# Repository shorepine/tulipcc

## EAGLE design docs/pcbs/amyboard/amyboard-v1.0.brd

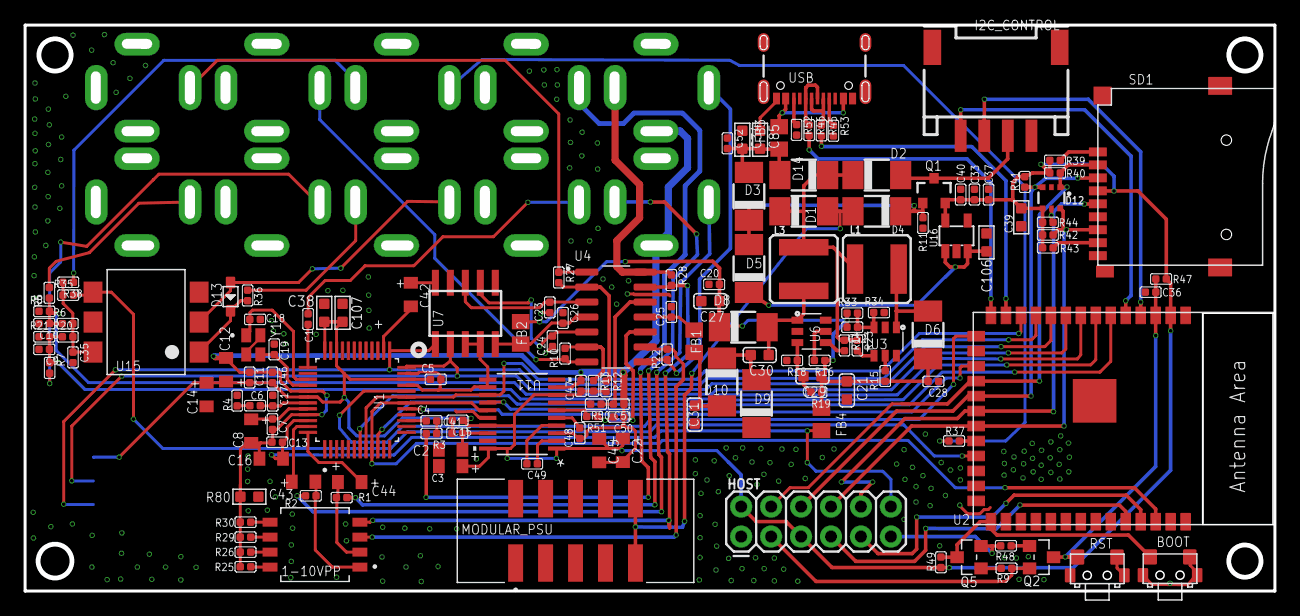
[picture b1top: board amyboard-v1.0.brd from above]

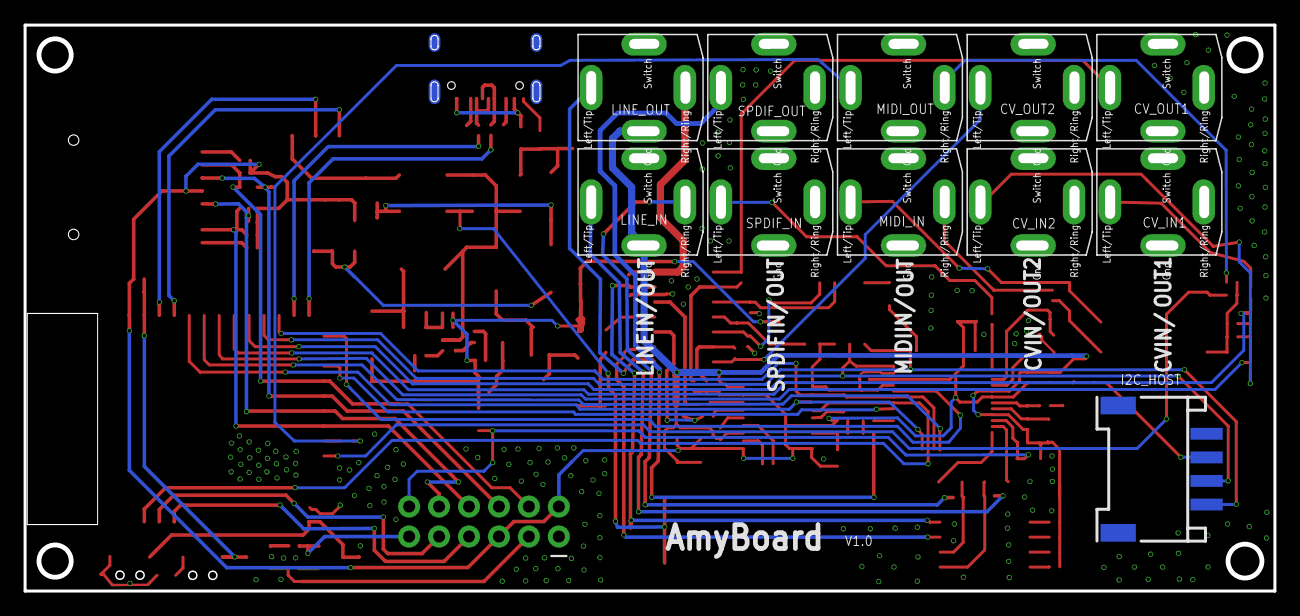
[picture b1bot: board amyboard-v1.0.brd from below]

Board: 2 copper layers, 106.0 x 48.0 mm, 155 parts (11 on the bottom side), 105 nets.

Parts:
1-10VPP: 218-4LPSTR; SW_218-4LPSTR
BOOT: TS24CA; 2*4*3.5MM
C1, C4, C5, C7, C11, C13, C15, C20, C23, C24, C25, C26, C28, C33, C35, C36, C37, C40, C41, C46, C47, C52: 100nF; DISCRETE_C0402
C2, C3, C8, C12, C14, C16, C22, C42, C43, C44, C45: 10uF/10V/TAN; SMC_Z
C6: 68nF; DISCRETE_C0402
C9, C10: 1nF; DISCRETE_C0402
C17: 4.7nF; DISCRETE_C0402
C18, C19: 10pF; DISCRETE_C0402
C21, C27, C30, C31: 22uF; C0603
C29: 22pF; C0603
C32: 22pF; DISCRETE_C0402
C34, C38, C39, C85: 10uF; DISCRETE_C0603
C48, C49: 2.2uF; DISCRETE_C0402
C50, C51: 2.2nF; DISCRETE_C0402
C106: 4.7uF/16V; 0603
C107: 10uF; 0603
CV_IN1, CV_IN2: NV-PJ3410_STEREO; NV-PJ3410_SOCKET
CV_OUT1, CV_OUT2: NV-PJ3410_STEREO; NV-PJ3410_SOCKET
D1, D2, D3, D4, D5, D6, D8, D9, D10, D14: SS54; DO-214AC
D12: SMF05C; SOT363
D13: 1N4148WS; SOD323
FB1, FB2, FB3, FB4: 100Mhz@120R; R0805
HOST: 2X6 FEMALE; 2X6
I2C_CONTROL, I2C_HOST: HW4-SMD-2.0-90D
L1: 4.7µH/±30%/3.4A; CR54
L3: 3.3µH/±30%/3.4A; CR54
LINE_IN: NV-PJ3410_STEREO; NV-PJ3410_SOCKET
LINE_OUT: NV-PJ3410_STEREO; NV-PJ3410_SOCKET
MIDI_IN: NV-PJ3410_STEREO; NV-PJ3410_SOCKET
MIDI_OUT: NV-PJ3410_STEREO; NV-PJ3410_SOCKET
MODULAR_PSU: 52601-G10-8LF; AMPHENOL_52601-G10-8LF
PCM5101: U11; PW20_TEX
Q1: AO3407; SOT23-3
Q2, Q5: S8050; SOT23
R1, R2, R22, R28: 51K; DISCRETE_R0402
R3: 150R; DISCRETE_R0402
R4: 680R; DISCRETE_R0402
R5, R7, R10, R27: 30K; DISCRETE_R0402
R6, R9, R12, R13, R20, R39, R40, R41, R42, R43, R47, R48, R49: 10K; DISCRETE_R0402
R8, R21, R34: 15K; DISCRETE_R0402
R11, R14, R23: 100K; DISCRETE_R0402
R15, R16: 0R; DISCRETE_R0402
R18: 12K; DISCRETE_R0402
R19: 228K; DISCRETE_R0402
R25, R26, R29, R30: 22K; DISCRETE_R0402
R33: 110K; DISCRETE_R0402
R35, R50, R51: 470R; DISCRETE_R0402
R36: 220R; DISCRETE_R0402
R37: 10R; DISCRETE_R0402
R38: 33R; DISCRETE_R0402
R44: NC; DISCRETE_R0402
R45, R46: 51R; DISCRETE_R0402
R52, R53: 5.1K; DISCRETE_R0402
R80: 0R; DISCRETE_R0603
RST: TS24CA; 2*4*3.5MM
SD1: SD; 9P-SMD-W/-RING
SPDIF_IN: NV-PJ3410_STEREO; NV-PJ3410_SOCKET
SPDIF_OUT: NV-PJ3410_STEREO; NV-PJ3410_SOCKET
U1: PCM9211PT; QFP50P900X900X160-48N
U2: ESP32­S2­SOLO; ESP32-­S2-­SOLO
U3, U6: HX3608; SOT-23-6
U4: TL074CD; SOIC127P600X175-14N
U7: GP8413; SOIC-10
U15: H11L1SR2M; SOP-6-2.54MM
U16: SPX3819; SOT23-5
USB: USB-C; USB-C-16P-5
Y1: 22.5792MHZ; XTAL_ABM10W-22.5792MHZ-8-K1Z-T3

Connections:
3.3V: C35.1, R6.2, R20.2, R35.1, R38.2, U15.6
3V3_IN: D2.A, I2C_CONTROL.3, Q1.3
5V: C13.1, C16.+, FB4.2, HOST.12, U1.46
5V_IN: C34.2, C52.2, C85.2, D3.A, D14.A, FB3.2
12V: C20.2, C21.1, C27.1, C28.2, C29.1, C32.2, D6.C, D8.C, FB2.1, FB4.1, R15.1, R16.1, R19.1, R33.1
12_IN: D1.A, D4.A, MODULAR_PSU.09, MODULAR_PSU.10
+3V3: C3.+, C5.1, C11.1, C12.+, C14.+, C15.1, C22.+, C33.2, C37.2, C38.1, C39.2, C40.1, C45.+, C46.1, C47.1, C107.1, D12.4, HOST.2, HOST.5, I2C_HOST.3, PCM5101.1, PCM5101.8, PCM5101.17, PCM5101.20, Q1.2, R12.2, R13.2, R39.2, R40.2, R41.2, R42.2, R43.2, R44.2, R47.2, R49.2, SD1.4, U1.22, U1.34, U1.36, U1.42, U2.2, U16.5
+12V: C26.2, FB2.2, U4.4, U7.5
-12V: C25.1, FB1.2, U4.11
ADC1: C10.1, R5.1, R6.1, R8.2, U2.9
ADC2: C9.1, R7.1, R20.1, R21.2, U2.8
AGND: C7.2, C8.-, C11.2, C12.-, C13.2, C16.-, C22.-, C45.-, C46.2, C47.2, C48.1, C50.1, C51.1, LINE_IN.GND, LINE_OUT.GND, PCM5101.3, PCM5101.9, R25.1, R26.1, R29.1, R30.1, R80.1, U1.41, U1.45
AMYIN: U1.17, U2.17
AMYOUT: PCM5101.14, U1.10, U2.6
AMY_FOLLOWER_SCL: I2C_CONTROL.1, U2.5
AMY_FOLLOWER_SDA: I2C_CONTROL.2, U2.4
BCLK: PCM5101.13, U1.8, U1.19, U2.12
CV_OUT1: CV_OUT1.LEFT/TIP, R27.1, U4.1
CV_OUT2: CV_OUT2.LEFT/TIP, R10.1, U4.7
DTR: HOST.11, Q5.2, R48.2
ENABLE: R14.2, U6.4
ENABLE1: R23.2, U3.4
GND: BOOT.1, BOOT.3, BOOT.4, C2.-, C3.-, C5.2, C9.2, C10.2, C14.-, C15.2, C17.1, C18.1, C19.1, C20.1, C21.2, C23.1, C24.1, C25.2, C26.1, C27.2, C28.1, C31.1, C33.1, C34.1, C35.2, C36.1, C37.1, C38.2, C39.1, C40.2, C41.1, C42.-, C52.1, C85.1, C106.2, C107.2, CV_IN1.GND, CV_IN2.GND, CV_OUT1.GND, CV_OUT2.GND, D9.C, D12.2, HOST.1, I2C_CONTROL.4, I2C_CONTROL.SS1, I2C_CONTROL.SS2, I2C_HOST.4, I2C_HOST.SS1, I2C_HOST.SS2, MIDI_IN.GND, MIDI_OUT.GND, MODULAR_PSU.01, MODULAR_PSU.02, MODULAR_PSU.03, MODULAR_PSU.04, MODULAR_PSU.05, MODULAR_PSU.06, MODULAR_PSU.07, MODULAR_PSU.08, PCM5101.10, PCM5101.11, PCM5101.12, PCM5101.16, PCM5101.19, R4.2, R8.1, R11.1, R18.2, R21.1, R34.2, R52.2, R53.2, R80.2, RST.1, RST.3, RST.4, SD1.6, SD1.G1, SD1.G2, SD1.G3, SD1.G4, SPDIF_IN.GND, SPDIF_OUT.GND, U1.21, U1.23, U1.26, U1.27, U1.38, U2.1, U2.40, U2.41, U3.2, U6.2, U7.3, U7.4, U7.6, U7.9, U15.5, U16.2, USB.GND, USB.GND2, Y1.2, Y1.4
I2C_SCL: I2C_HOST.1, U1.25, U2.11, U7.1
I2C_SDA: I2C_HOST.2, U1.24, U2.10, U7.2
IO0: BOOT.2, Q5.3, R49.1, U2.27
IO19: R45.2, U2.13
IO20: R46.2, U2.14
LIN: LINE_IN.LEFT/TIP, R2.2
LINX: C43.+, U1.47
LOUT: LINE_OUT.LEFT/TIP, R22.1, U4.8
LOUT_2V: C50.2, R51.1, U4.10
LRC: PCM5101.15, U1.9, U1.18, U2.38
MCLK: U1.20, U2.15
MIDI_IN: R35.2, U2.23, U15.4
MIDI_OUT: R37.2, U2.22
MPIO: U1.7, U2.7
unnamed: C1.1, U1.37
unnamed: C4.2, R3.1
unnamed: C4.1, U1.15
unnamed: 1-10VPP.1, C43.-, R2.1
unnamed: 1-10VPP.2, C44.-, R1.1
unnamed: C7.1, C8.+, U1.44
unnamed: C6.2, C17.2, U1.43
unnamed: C6.1, R4.1
unnamed: CV_IN2.LEFT/TIP, R7.2
unnamed: D6.A, L1.P$2, U3.1
unnamed: C31.2, D10.A, FB1.1
unnamed: C23.2, U4.3, U7.8
unnamed: CV_IN1.LEFT/TIP, R5.2
unnamed: C24.2, U4.5, U7.7
unnamed: C30.1, D8.A, L3.P$2, U6.1
unnamed: C42.+, U7.10
unnamed: D3.C, D4.C, D5.A, Q1.1, R11.2
unnamed: C106.1, D5.C, U16.1, U16.3
unnamed: C32.1, R33.2, R34.1, U3.3
unnamed: C29.2, R18.1, R19.2, U6.3
unnamed: R16.2, U6.5
unnamed: C30.2, D9.A, D10.C
unnamed: R10.2, R13.1, U4.6
unnamed: R15.2, U3.5
unnamed: R12.1, R27.2, U4.2
unnamed: Q2.1, R48.1
unnamed: 1-10VPP.5, R30.2
unnamed: 1-10VPP.6, R29.2
unnamed: Q5.1, R9.1
unnamed: R53.1, USB.A5
unnamed: R52.1, USB.B5
unnamed: 1-10VPP.8, R25.2
unnamed: 1-10VPP.7, R26.2
unnamed: FB3.1, USB.VBUS1, USB.VBUS2
unnamed: 1-10VPP.3, R22.2, U4.9
unnamed: 1-10VPP.4, R28.2, U4.13
unnamed: C2.+, C41.2, PCM5101.18
unnamed: PCM5101.7, R50.2
unnamed: C49.2, PCM5101.4
unnamed: C49.1, PCM5101.2
unnamed: D13.+, MIDI_IN.LEFT/TIP, U15.2
unnamed: MIDI_IN.RIGHT/RING, R36.1
unnamed: D13.-, R36.2, U15.1
unnamed: MIDI_OUT.LEFT/TIP, R37.1
unnamed: MIDI_OUT.RIGHT/RING, R38.1
unnamed: R39.1, SD1.1
unnamed: R43.1, SD1.8
OUTL: PCM5101.6, R51.2
RESET: C36.2, Q2.3, R47.1, RST.2, U2.3
RIN: LINE_IN.RIGHT/RING, R1.2
RINX: C44.+, U1.48
ROUT: LINE_OUT.RIGHT/RING, R28.1, U4.14
ROUT_2V: C51.2, R50.1, U4.12
RTS: HOST.3, Q2.2, R9.2
RXD/IO44: HOST.7, U2.36
SPDIFIN_SIGNAL: C1.2, SPDIF_IN.LEFT/TIP
SPDIFOUT_SIGNAL: R3.2, SPDIF_OUT.LEFT/TIP
SPI0_CS0: D12.1, HOST.4, R40.1, SD1.2, U2.18
SPI0_MISO: D12.6, HOST.8, R42.1, SD1.7, U2.21
SPI0_MOSI: D12.3, HOST.6, R41.1, SD1.3, U2.19
SPI0_SCK: D12.5, HOST.10, R44.1, SD1.5, U2.20
TXD/IO43: HOST.9, U2.37
USB_D+: R46.1, USB.A6, USB.B6
USB_D-: R45.1, USB.A7, USB.B7
VNEG: C48.2, PCM5101.5
VPWR: D1.C, D2.C, D14.C, L1.P$1, L3.P$1, R14.1, R23.1
XTI: C18.2, U1.39, Y1.1
XTO: C19.2, U1.40, Y1.3

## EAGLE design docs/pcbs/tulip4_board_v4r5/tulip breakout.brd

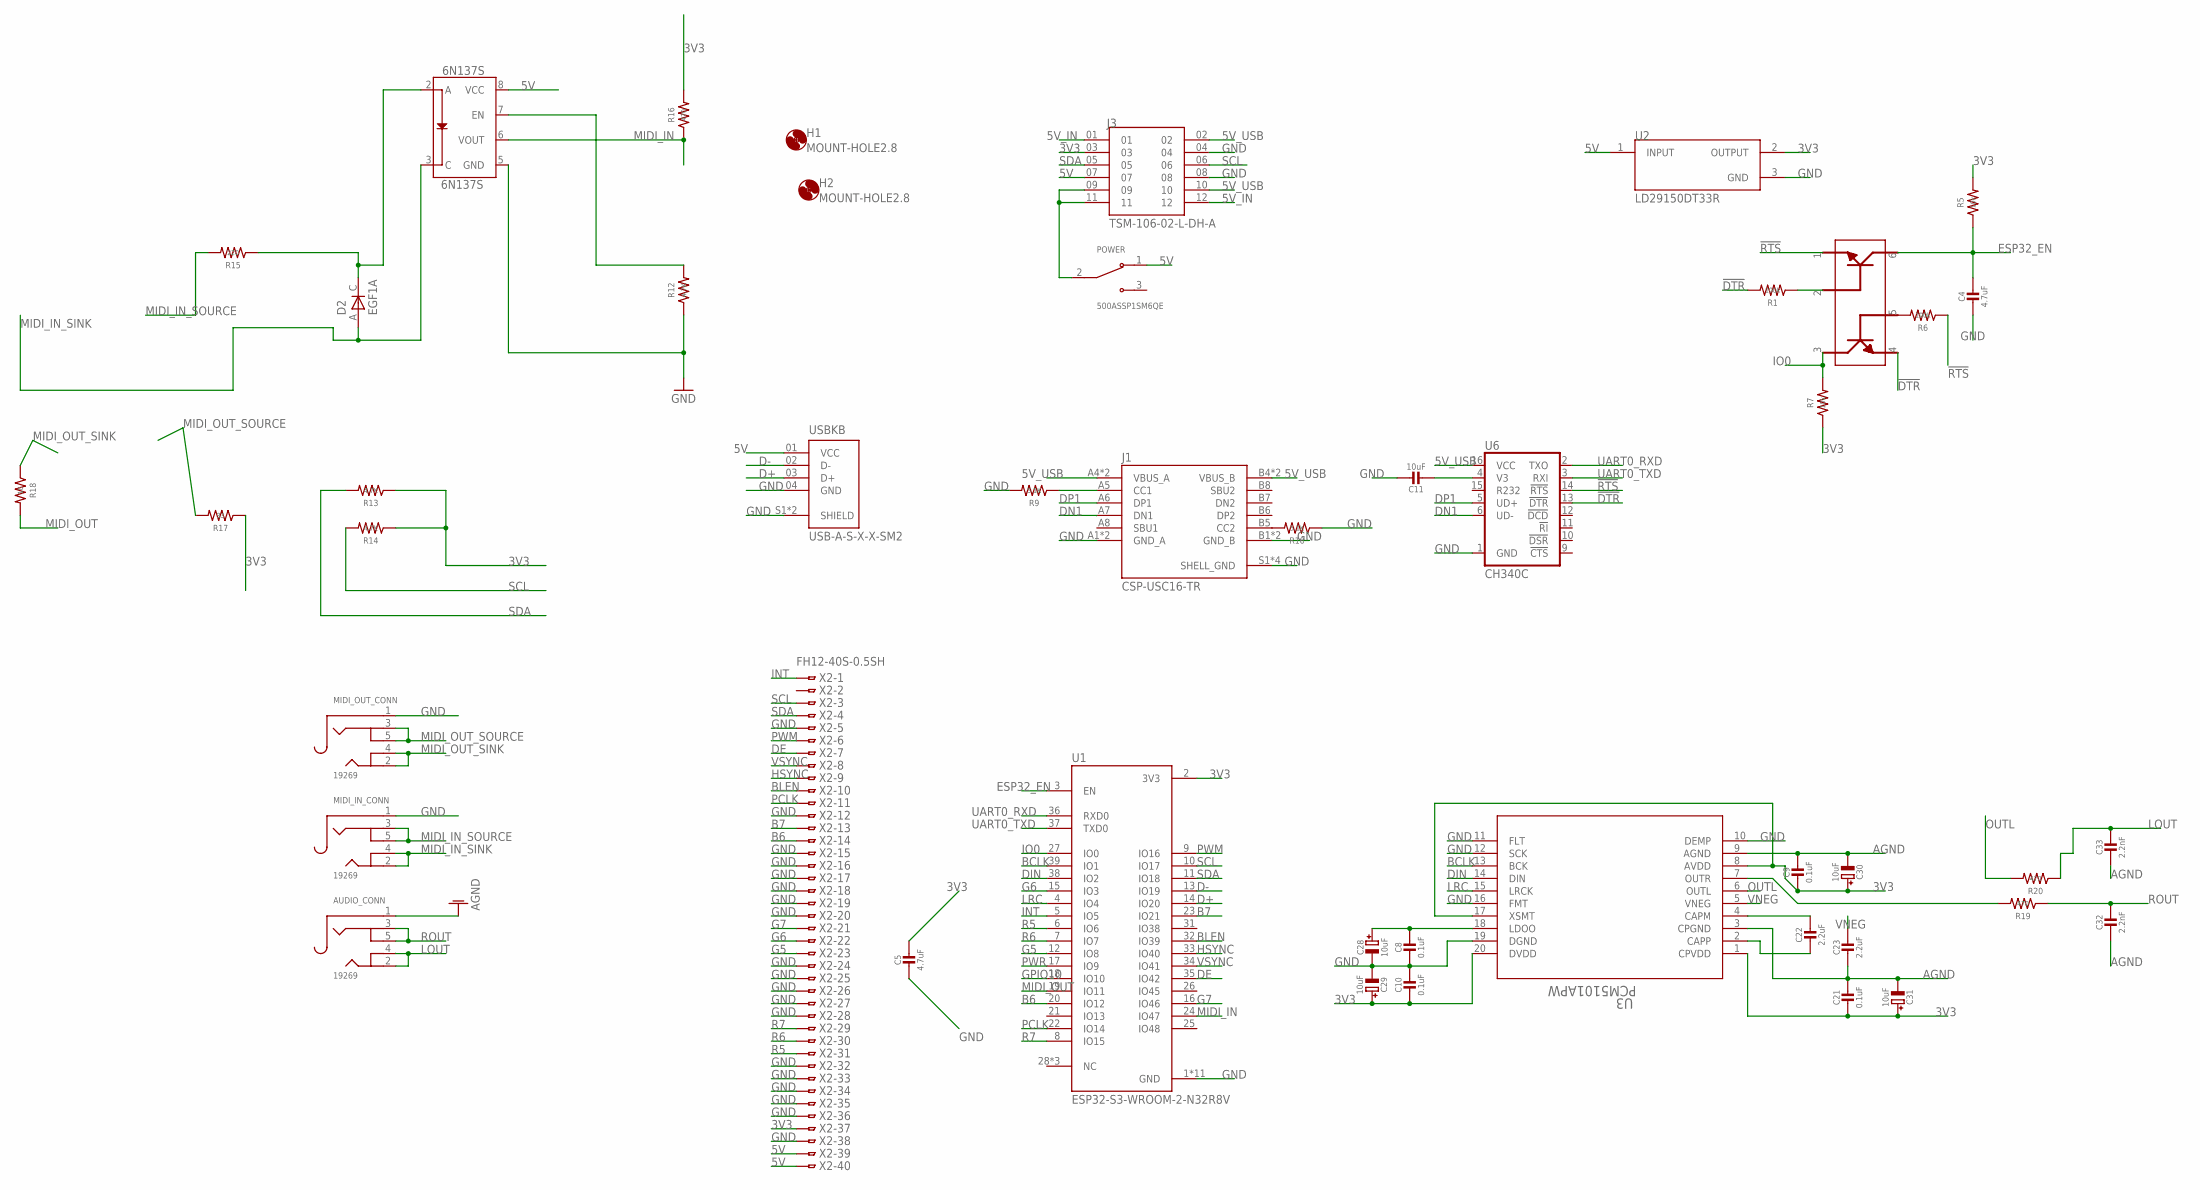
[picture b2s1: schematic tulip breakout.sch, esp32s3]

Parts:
6N137S: 6N137S; 8-SMD
AUDIO_CONN: 19269; 4UCONN_19269
C4, C5: 4.7uF; 0805-NO
C8, C9, C10, C21: 0.1uF; 0805-NO
C11: 10uF; 0805-NO
C22, C23: 2.2uF; 0805-NO
C28, C29, C30, C31: 10uF; PANASONIC_C
C32, C33: 2.2nF; 0805-NO
D2: EGF1A; DIOM449X264X300L114X135N
H1, H2: MOUNT-HOLE2.8; 2,8
J1: CSP-USC16-TR; VALCON_CSP-USC16-TR
J3: TSM-106-02-L-DH-A; SAMTEC_TSM-106-02-L-DH-A
MIDI_IN_CONN: 19269; 4UCONN_19269
MIDI_OUT_CONN: 19269; 4UCONN_19269
POWER: 500ASSP1SM6QE; SW_500ASSP1SM6QE
R1, R6: 100k; R0805
R5, R7: 10k; R0805
R9, R10: 5.1K; R0805
R12, R13, R14: 4.7K; R0805
R15: 220; R0805
R16, R19, R20: 470; R0805
R17: 33; R0805
R18: 10; R0805
RESET: MBT3904DW1T1G; SOT236
U1: ESP32-S3-WROOM-2-N32R8V; XCVR_ESP32-S3-WROOM-2-N32R8V
U2: LD29150DT33R; DPAK456P972X240-3N
U3: PCM5101APW; PW20_TEX
U6: CH340C; SO016
USBKB: USB-A-S-X-X-SM2; SAMTEC_USB-A-S-X-X-SM2
X2: FH12-40S-0.5SH

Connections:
5V: 6N137S.8 (VCC), J3.07, POWER.1 (NC), U2.1 (INPUT), USBKB.01 (VCC), X2.39, X2.40
5V_IN: J3.01, J3.12
!DTR: R1.2, RESET.4, U6.13 (!DTR)
!RTS: R6.1, RESET.1, U6.14 (!RTS)
AGND: AUDIO_CONN.1, C9.1, C21.1, C23.2, C30.-, C31.-, C32.2, C33.2, U3.3 (CPGND), U3.9 (AGND)
B6: U1.20 (IO12), X2.14
B7: U1.23 (IO21), X2.13
BCLK: U1.39 (IO1), U3.13 (BCK)
BLEN: U1.32 (IO39), X2.10
D+: U1.14 (IO20), USBKB.03 (D+)
D-: U1.13 (IO19), USBKB.02 (D-)
DE: U1.35 (IO42), X2.7
DIN: U1.38 (IO2), U3.14 (DIN)
DN1: J1.A7 (DN1), U6.6 (UD-)
DP1: J1.A6 (DP1), U6.5 (UD+)
ESP32_EN: C4.1, R5.1, RESET.6, U1.3 (EN)
G5: U1.12 (IO8), X2.23
G6: U1.15 (IO3), X2.22
G7: U1.16 (IO46), X2.21
GND: 6N137S.5 (GND), C4.2, C5.2, C8.2, C10.1, C11.1, C28.-, C29.-, J1.A1 (GND_A), J1.A12 (GND_A), J1.B1 (GND_B), J1.B12 (GND_B), J1.S1 (SHELL_GND), J1.S2 (SHELL_GND), J1.S3 (SHELL_GND), J1.S4 (SHELL_GND), J3.04, J3.08, MIDI_IN_CONN.1, MIDI_OUT_CONN.1, R9.2, R10.1, R12.1, U1.1 (GND), U1.40 (GND), U1.41_1 (GND), U1.41_2 (GND), U1.41_3 (GND), U1.41_4 (GND), U1.41_5 (GND), U1.41_6 (GND), U1.41_7 (GND), U1.41_8 (GND), U1.41_9 (GND), U2.3 (GND), U3.10 (DEMP), U3.11 (FLT), U3.12 (SCK), U3.16 (FMT), U3.19 (DGND), U6.1 (GND), USBKB.04 (GND), USBKB.S1 (SHIELD), USBKB.S2 (SHIELD), X2.5, X2.12, X2.15, X2.16, X2.17, X2.18, X2.19, X2.20, X2.24, X2.25, X2.26, X2.27, X2.28, X2.32, X2.33, X2.34, X2.35, X2.36, X2.38
GPIO10: U1.18 (IO10)
HSYNC: U1.33 (IO40), X2.9
INT: U1.5 (IO5), X2.1
IO0: R7.2, RESET.3, U1.27 (IO0)
LOUT: AUDIO_CONN.2, AUDIO_CONN.4, C33.1, R20.1
LRC: U1.4 (IO4), U3.15 (LRCK)
MIDI_IN: 6N137S.6 (VOUT), R16.1, U1.24 (IO47)
MIDI_IN_SINK: 6N137S.3 (C), D2.A, MIDI_IN_CONN.2, MIDI_IN_CONN.4
MIDI_IN_SOURCE: MIDI_IN_CONN.3, MIDI_IN_CONN.5, R15.2
MIDI_OUT: R18.2, U1.19 (IO11)
MIDI_OUT_SINK: MIDI_OUT_CONN.2, MIDI_OUT_CONN.4, R18.1
MIDI_OUT_SOURCE: MIDI_OUT_CONN.3, MIDI_OUT_CONN.5, R17.2
unnamed: R1.1, RESET.2
unnamed: R6.2, RESET.5
unnamed: J1.B5 (CC2), R10.2
unnamed: C8.1, C28.+, U3.18 (LDOO)
unnamed: R19.2, U3.7 (OUTR)
unnamed: J3.09, J3.11, POWER.2 (COM)
unnamed: C22.1, U3.4 (CAPM)
unnamed: C22.2, U3.2 (CAPP)
unnamed: 6N137S.2 (A), D2.C, R15.1
unnamed: 6N137S.7 (EN), R12.2
unnamed: C11.2, U6.4 (V3)
unnamed: J1.A5 (CC1), R9.1
OUTL: R20.2, U3.6 (OUTL)
PCLK: U1.22 (IO14), X2.11
PWM: U1.9 (IO16), X2.6
PWR: U1.17 (IO9)
R5: U1.6 (IO6), X2.31
R6: U1.7 (IO7), X2.30
R7: U1.8 (IO15), X2.29
ROUT: AUDIO_CONN.3, AUDIO_CONN.5, C32.1, R19.1
SCL: J3.06, R14.2, U1.10 (IO17), X2.3
SDA: J3.05, R13.2, U1.11 (IO18), X2.4
UART0_RXD: U1.36 (RXD0), U6.2 (TXO)
UART0_TXD: U1.37 (TXD0), U6.3 (RXI)
VNEG: C23.1, U3.5 (VNEG)
VSYNC: U1.34 (IO41), X2.8

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
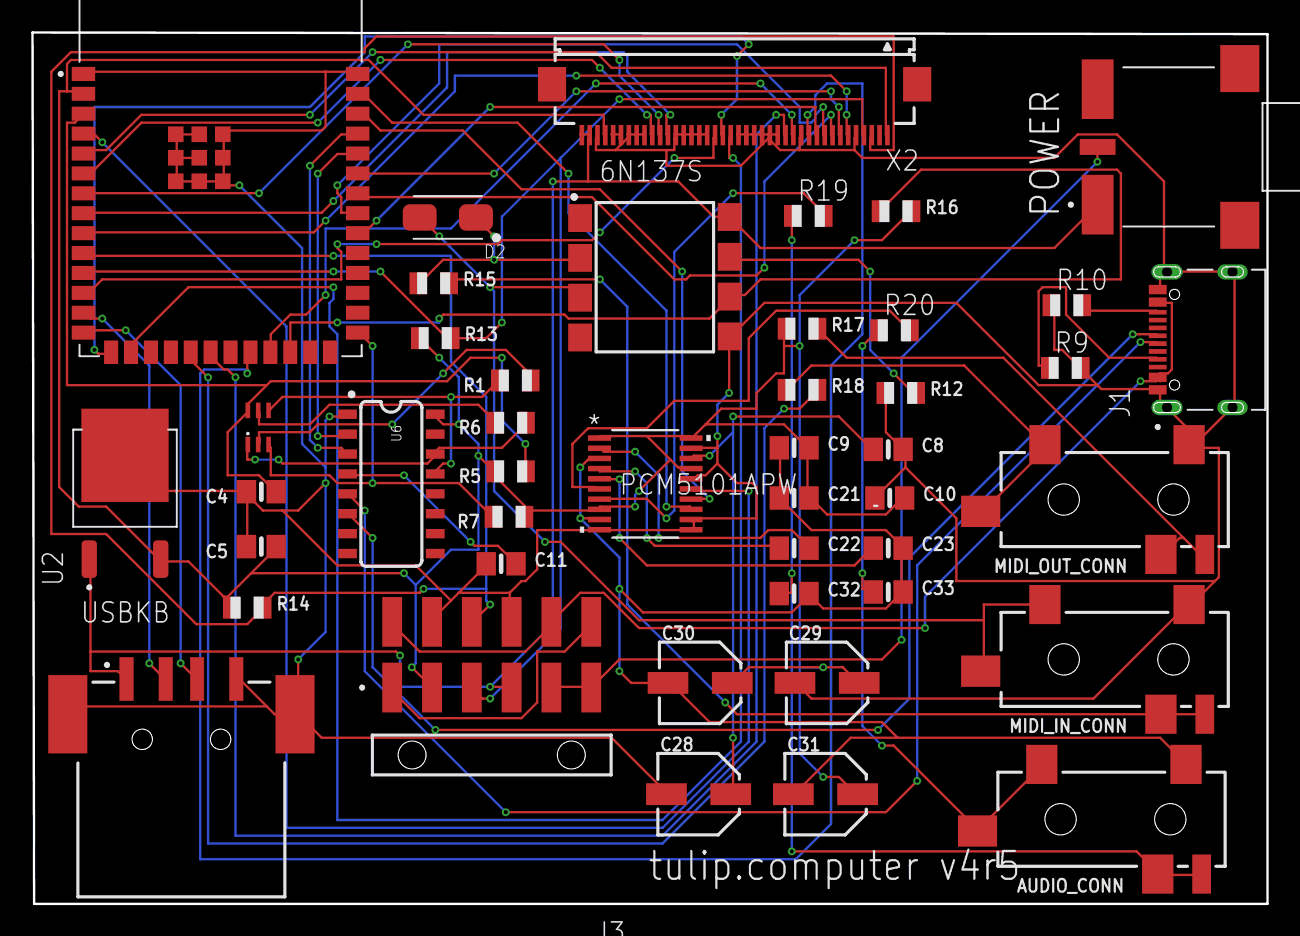
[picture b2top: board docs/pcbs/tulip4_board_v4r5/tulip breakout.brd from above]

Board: 2 copper layers, 78.8 x 55.6 mm, 45 parts (0 on the bottom side), 58 nets.

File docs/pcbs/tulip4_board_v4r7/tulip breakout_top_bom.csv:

Comment,Designator,Footprint,LCSC Part #
0.1uF,C8 C9 C10 C21,0805-NO,
2.2nF,C32 C33,0805-NO,
2.2uF,C22 C23,0805-NO,
4.7K,R12 R13 R14,R0805,
4.7uF,C4 C5,0805-NO,
5.1K,R9 R10,R0805,
6N137S,6N137S,8-SMD,
10,R18,R0805,
10k,R5 R7,R0805,
10uF,C11,0805-NO,
10uF,C28 C29 C30 C31,PANASONIC_C,
33,R17,R0805,
100k,R1 R6,R0805,
220,R15,R0805,
470,R16 R19 R20,R0805,
500ASSP1SM6QE,POWER,SW_500ASSP1SM6QE,
19269,AUDIO_CONN MIDI_IN_CONN MIDI_OUT_CONN,4UCONN_19269,
CH340C,U6,SO016,
CSP-USC16-TR,J1,VALCON_CSP-USC16-TR,
EGF1A,D2,DIOM449X264X300L114X135N,
ESP32-S3-WROOM-2-N32R8V,U1,XCVR_ESP32-S3-WROOM-2-N32R8V,
FH12-40S-0.5SH,X2,FH12-40S-0.5SH,
LD29150DT33R,U2,DPAK456P972X240-3N,
MBT3904DW1T1G,RESET,SOT236,
PCM5101APW,U3,PW20_TEX,
TSM-106-02-L-DH-A,J3,SAMTEC_TSM-106-02-L-DH-A,
USB-A-S-X-X-SM2,USBKB,SAMTEC_USB-A-S-X-X-SM2,

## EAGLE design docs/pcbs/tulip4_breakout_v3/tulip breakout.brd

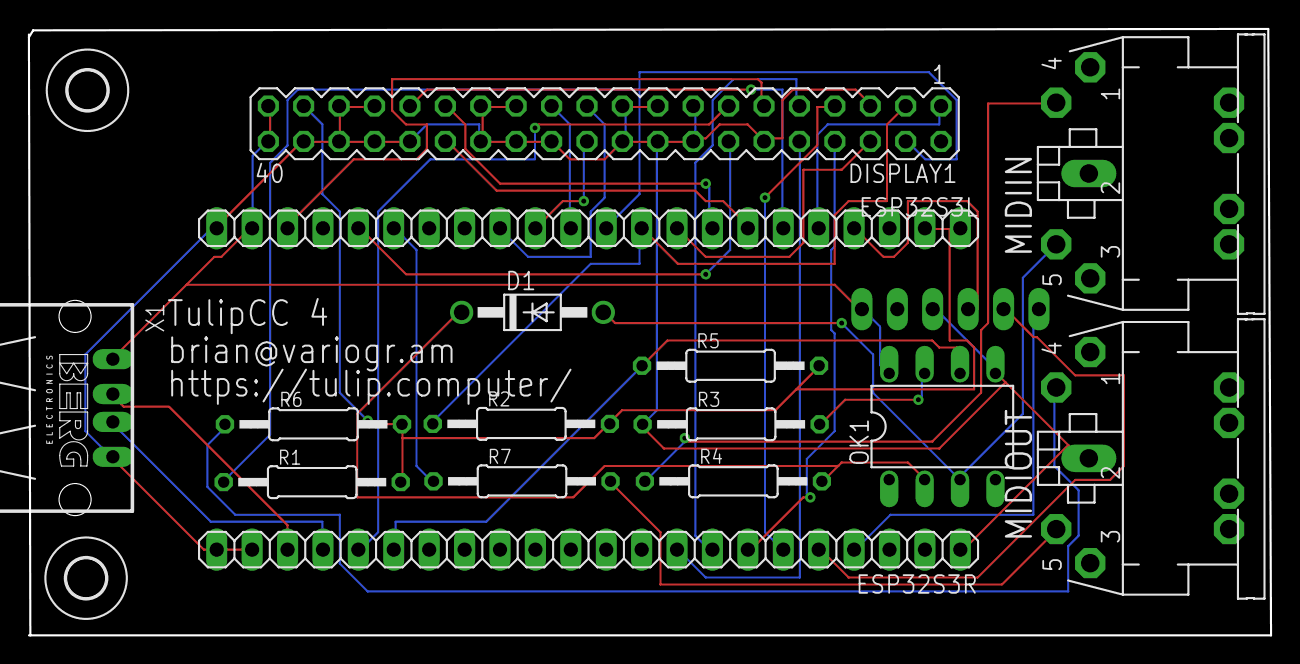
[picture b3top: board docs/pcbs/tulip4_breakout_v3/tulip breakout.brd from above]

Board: 2 copper layers, 89.1 x 43.5 mm, 18 parts (1 on the bottom side), 33 nets.

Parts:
AUDIO3: 1X06
D1: 1N4004; DO41-10
DISPLAY1: MA20-2
ESP32S3L, ESP32S3R: 1X22
H1, H2: MOUNT-HOLE2.8; 2,8
MIDIIN: MIDIJACK; CP-2350
MIDIOUT: MIDIJACK; CP-2350
OK1: 6N138; DIL08
R1, R2, R3: 4.7K; 0207/12
R4: 220; 0207/12
R5: 470; 0207/12
R6: 33; 0207/12
R7: 10; 0207/12
X1: PN87520

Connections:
3V3: DISPLAY1.37, ESP32S3L.1, ESP32S3L.2, R1.2, R2.2, R5.2, R6.2
5V: AUDIO3.1, DISPLAY1.39, DISPLAY1.40, ESP32S3L.21, OK1.8, X1.1
B6: DISPLAY1.14, ESP32S3L.18
B7: DISPLAY1.13, ESP32S3R.18
BCLK: AUDIO3.6, ESP32S3R.4
BLEN: DISPLAY1.10, ESP32S3R.9
D+: ESP32S3R.19, X1.3
D-: ESP32S3R.20, X1.2
DE: DISPLAY1.7, ESP32S3R.6
DIN: AUDIO3.5, ESP32S3R.5
G5: DISPLAY1.23, ESP32S3L.12
G6: DISPLAY1.22, ESP32S3L.13
G7: DISPLAY1.21, ESP32S3L.14
GND: AUDIO3.3, DISPLAY1.5, DISPLAY1.12, DISPLAY1.15, DISPLAY1.16, DISPLAY1.17, DISPLAY1.18, DISPLAY1.19, DISPLAY1.20, DISPLAY1.24, DISPLAY1.25, DISPLAY1.26, DISPLAY1.27, DISPLAY1.28, DISPLAY1.32, DISPLAY1.33, DISPLAY1.34, DISPLAY1.35, DISPLAY1.36, DISPLAY1.38, ESP32S3L.22, ESP32S3R.1, ESP32S3R.21, ESP32S3R.22, MIDIOUT.2, OK1.5, R3.1, X1.4
HSYNC: DISPLAY1.9, ESP32S3R.8
INT: DISPLAY1.1, ESP32S3L.5
LRC: AUDIO3.4, ESP32S3L.4
MIDI_IN: ESP32S3R.17, OK1.6, R5.1
MIDI_OUT: ESP32S3L.17, R7.1
unnamed: MIDIIN.4, R4.1
unnamed: D1.C, OK1.2, R4.2
unnamed: D1.A, MIDIIN.5, OK1.3
unnamed: OK1.7, R3.2
unnamed: MIDIOUT.5, R7.2
unnamed: MIDIOUT.4, R6.1
PCLK: DISPLAY1.11, ESP32S3L.20
PWM: DISPLAY1.6, ESP32S3L.9
R5: DISPLAY1.31, ESP32S3L.6
R6: DISPLAY1.30, ESP32S3L.7
R7: DISPLAY1.29, ESP32S3L.8
SCL: DISPLAY1.3, ESP32S3L.10, R2.1
SDA: DISPLAY1.4, ESP32S3L.11, R1.1
VSYNC: DISPLAY1.8, ESP32S3R.7

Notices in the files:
parts and their libraries:
microbuilder: This work is placed in the public domain, and may be freely used for commercial and non-commercial work with the following conditions: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
SparkFun-Coils: Licensing: Creative Commons ShareAlike 4.0 International - https://creativecommons.org/licenses/by-sa/4.0
